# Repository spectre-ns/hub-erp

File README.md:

# hub-erp: an open-source ERP and quality management system where your SOPs are the configuration, and AI agents work under the same rules as people

**hub-erp** is an open-source, self-hosted ERP and quality management system (QMS) built around one idea: the
procedures you already write — SOPs, policies, work instructions — should *be* the system's configuration, not a
description of it. Change a sentence in a policy, put the change through review and approval, and the system's
permissions, routing, approval limits and workflows change with it. AI agents ("cogs") take on routine work beside
your people, as accountable team members: they hold roles, follow the same procedures, act only within criteria the
policy sets, and leave the same signed record a person would.

It is a working prototype, built to explore how far that idea goes in a real business system: purchasing, inventory,
document control, change control, nonconformances and CAPA, complaints, internal audits, management review, design
control, calibration and training.

## What it attempts

- **SOPs as the single source of truth.** Policies are written in plain prose. The hub compiles them into the rules
  it enforces — every rule cites the sentence it came from — and a released policy version is immutable and
  content-addressed. An edit made in Settings or one of the editors becomes a change on a change order, and a cog
  writes it back into the SOP's prose for review, so the configuration never drifts away from the procedures. A
  picture put into an SOP is a question for a person, and a citation of another document is checked, linked, and
  flagged to the SOP's owner when the cited document is retired or superseded.
- **AI agents as governed team members.** Cogs are members of the organization with roles, like anyone else, and no
  outsized permissions. Senior cogs (hosted models) read policy changes and propose the configuration they imply;
  junior cogs (local models) review changes, answer questions and take routine approvals — each within criteria a
  guard checks without any model, so the impact of a wrong judgement stays small. A cog never signs a change to the
  system.
- **Change control for the system itself.** Every configuration change goes through a change order: the cogs compile
  the diff and raise questions, a review panel weighs in, people decide each item (a widening of anyone's authority
  needs two policy owners, and whoever made a change never decides it alone), the change order is signed, and a
  deterministic release — no AI in any step that changes the system — puts exactly what was signed into force.
- **Evidence by default.** Every step of every process lands on an append-only, chained, signed Track; decisions are
  electronic signatures that record who decided, what they saw and what they meant. The design aims at what quality
  standards such as ISO 9001 and ISO 13485 expect of records and signatures.
- **People where judgement matters.** Routine, well-bounded work flows to cogs; anything outside their criteria goes to
  a person, with the reason shown: each item's run page explains, rule by rule, who its approval went to and why.

## Who it is for

- Organizations in quality-driven and regulated industries — manufacturing, engineering, medical devices — that want
  agents to take on routine work without giving up control or traceability.
- Developers and researchers exploring how to govern LLM agents inside business systems: policy-as-prose, guardrails
  that are not models, human approval of configuration, and audit trails that hold up.

hub-erp is a prototype: it has not been validated for production or regulated use, and adopting it for that would
mean validating it as your own quality system requires.

## Make it yours

hub-erp is released under the [MIT license](LICENSE). Every organization's processes are different, so the intent is
that you take this code as a starting point and shape it — the SOPs, the record types, the workflows and the code
itself — around the way your business actually works. The MIT license lets you do that and keep your changes to
yourself: you are free to modify it for your own processes without publishing those modifications. If you build
something you would like to share, contributions are warmly welcome, but never required. (Do keep the license notice
in copies of the code.)

## How it works: six parts

| Part | What it is |
|---|---|
| **Frames** | SOPs, policies and work instructions in prose, compiled into an immutable **policy release** |
| **Cogs** | AI team members with roles: senior cogs compile policy changes, junior cogs review and do routine work |
| **Ops** | Business processes, run as workflows under the release in force; the hub's own automations are Ops too |
| **Guards** | Deterministic checks with no model: grammar and grounding, consistency, widenings, document references, permissions, criteria |
| **Gates** | Where a person, a cog within its criteria, or a committee decides; each decision is an electronic signature |
| **Tracks** | The append-only, chained, signed record of every run |

One record system and one document management system (DMS) span every module. Standard-library Python, SQLite and
files, packaged in a single Docker image. Developer notes: [DEV-NOTES.md](DEV-NOTES.md); for coding agents:
[AGENTS.md](AGENTS.md); the design of change control: [docs/design/change-control.md](docs/design/change-control.md);
the user manual: [docs/manual/](docs/manual/).

## Run it

```bash
docker compose up --build        # http://localhost:8080/ asks who you are; e.g. /?as=alice
```

First start seeds the kernel, installs the ISO 9001 profile, compiles and
releases the first policy release with the two seeded policy owners (bob and
carol), and then makes the SOPs documents: from then on **every configuration
change goes through a change order** (Quality > Change orders); see "Once the
SOPs are documents" below. If that first release fails (for example an org
model with nobody in a routed role) the container prints the Frame to fix,
notes it in `state/.bootstrap-failed`, and still serves the shell with no
release in effect; fix the Frame and run
`docker compose exec hub hubproto bootstrap-release --as bob --second carol`
(run again on a released hub whose SOPs are not documents yet, it converts them).
State lives in the `hub-state` volume and the hub's Frames in the `hub-frames`
volume: the first start fills it with the Frames the image ships, and every
release writes the released texts into it, never into the checkout (the
repository's `frames/` are the example Frames, not a hub's policy). A newer
image's Frames reach a running hub only through a change order. To work on the
checkout's `frames/` and `profiles/` folders from Docker, add
`docker-compose.frames-dir.yml`: a separate development hub (its own Compose
project, containers, image tag and ports; see its header), never the live one. A hub
whose Frames were bind-mounted from the checkout before (issue #5) is moved with
`docs/rollout/frames-volume.md`.

Without Docker (`--root` is the directory holding `frames/` and `state/`;
set `HUBPROTO_ROOT` or pass `--root` when you are not in it):

```bash
python -m venv .venv && . .venv/bin/activate && pip install -e ".[test]"
hubproto init && hubproto seed iso9001 && hubproto bootstrap-release --as bob --second carol
hubproto shell
```

For development, run as many hubs as you like beside the Docker one, each from a
worktree's code, released and with a little demo data, on its own port from 8100
(never 8080, 9980 or 11434), with stand-in models; see DEV-NOTES.md, "Running hubs
for development and for agents" (in a worktree, `python -m hubproto dev ...` runs
that worktree's command line):

```bash
hubproto dev serve --detach --name ws12   # prints http://127.0.0.1:81xx/; open it with ?as=carol
hubproto dev list                         # what runs: name, port, pid, branch, commit, url
hubproto dev stop ws12 && hubproto dev clean ws12
```

Tests: `pip install -r requirements-dev.txt` (pytest and pytest-xdist, development
only), then `python -m pytest -q -n auto` (parallel; without `-n auto` the suite runs
serially and passes that way too).

`hubproto --help` lists every verb in the order an operator uses them, and
`hubproto <verb> --help` explains each flag. Exit codes: 0 done; 1 the hub
refused or the outcome is a failure (error findings, `DENIED`, a failed run);
2 a mistake in the command (unknown id, bad JSON, missing file, wrong root).
A wrong `--root` is refused ("no hub at ..."), never filled with an empty hub.

## After changing Frames (a hub that keeps the Frame files)

A hub bootstrapped with `hubproto bootstrap-release --as bob --second carol
--keep-frame-files "<why>"` (or `sopdocs.keep_frame_files`) skips the
conversion: the Frame files stay the source and the policy owners release
changes without change orders. It is recorded and `status` shows it on every
run; it is meant for work on the Frames themselves and for the test suites
(`tests/conftest.py`'s `release_all` opts out this way), and it ends with
`hubproto sops convert`. On such a hub, edit a sentence in `frames/` on the
host (in Docker: on a development hub from `docker-compose.frames-dir.yml`,
or in the `hub-frames` volume), then compile, have it reviewed and release it. Until the release, the
shell and every run keep applying the release in force (the Frames as they
were released), and on its next start the container says so: `hubproto status
--check` lists the files that differ and prints these commands.

```bash
docker compose exec hub hubproto compile                                  # exit 1 and no release while there are error findings
docker compose exec hub hubproto proposals                                # what is waiting, by number
docker compose exec hub hubproto proposal 3                               # each change with its sentence, file:line and decisions
docker compose exec hub hubproto review 3 --as bob --approve-all --meaning "..."
docker compose exec hub hubproto review 3 --as carol --approve-all        # a widening (a new allow, member, cog route) needs two owners
docker compose exec hub hubproto release 3 --as bob                       # bob or carol: a policy owner of the release in force
docker compose exec hub hubproto releases                                 # versions v1, v2, ... with the digest after
docker compose exec hub hubproto release-diff v2                          # sentences added, removed, changed against v1, and who signed
docker compose run --rm tick                                              # escalate overdue items
```

`compile` refuses to release a heading or a rule-like sentence it could not
read (a `grammar` error with the file and line), a stale proposal (compiled
against an older release than the one in force) is refused with "compile
again", and a release that only re-renders a process is reported as
"re-rendered, no semantic change" instead of a pair of add/remove changes.

Prose that is not in the sentence shapes is read by the compile-frame committee, **as a diff**: an SOP whose text
is the one in force keeps the rules the release read from it, with no model call; a changed SOP's readers get the
unified diff (with line numbers) and the rules in force from it, and answer with rules to add, remove or change and
with **questions** where the changed prose is ambiguous (`proposal["questions"]`; members asking the same thing about
a line make one question; a question the next compile no longer raises is closed). A large diff is read in parts that
fit the model's window. Every change on a proposal says where it came from (`origin`: the SOP, line, words and
reader) and, for a rule a model read, what it means in the hub's own words (`origin.explained`); a reading that drops
or adds a "not" carries a `negation` warning. A rule that only moved in its file (a process below inserted lines) is
listed as moved, not as a change to decide. Direct changes on a change order are put into prose by the qa-manager cog
and compiled back to check they give exactly that rule and nothing else (`hubproto/prose_drafting.py`); the lines it
drafts are credited to it. A reading may touch only the lines that changed: anything else is refused as an `outside-diff`
question (the SOP text is fenced as data in the readers' prompts, so words aimed at the readers are ignored and reported).
A changed sentence that reads like a rule and from which nothing was read, by the grammar or the committee, is a
blocking `unread-rule` question for the committee's chair, also when no model reads here (`convention`).

**The committee reads by consensus.** It is defined on the `senior-cogs` group (organization model, `## Groups`):
the **senior** cogs `senior-organization` and `senior-qa-manager`, bundled with Claude Opus (`claude-opus-5-5`); the
**junior** cogs (`organization`, `qa-manager` and the others, group `junior-cogs`) stay on the local model for
day-to-day work. Each member reads with the model its profile bundles it with,
from its own perspective (its About text, its persona's behaviour and the roles it holds); the diff, the rules in force
and the answer format are the same for every member, so their readings stay comparable.
A rule goes in only when every member reads it the same way; where members read a line differently, the proposal gets
a `disagreement` question quoting the line and each member's reading, for a person to decide. A member whose model is
not available here (not installed, Ollama down, or a `claude-*` model or one of Ollama's cloud models, such as
`gemma4:cloud`, while hosted models are off) is a
`member-unavailable` question naming the committee's chair (`Chair: carol`), who intervenes: the prose of a changed SOP
is not read until it is. **The senior cogs are available only where the administrator has switched hosted models on**
(`HUBPROTO_HOSTED_MODELS=on` with `ANTHROPIC_API_KEY`, under the IT SOP); the call goes through the hub's model gateway
to the Anthropic Messages API. Without them the compiler reads the sentence shapes only and asks about changed prose.
The committee's members change through a change order (the `senior-cogs` group, or a cog's `Model:` line).

**Groups and committees** (change control 11) are also used in processes and on change orders: a process step written
`the design-review committee decides` waits for every member of the committee (people and cogs) and moves only when all
agree; an objection with its reason returns the item; when a cog member's criteria do not hold or a member is late, the
committee's chair intervenes (decide in that member's place, extend the due date, or return the item). A change-control
review sentence may name a committee as reviewers. See DEV-NOTES.md, "Groups and committees".

| Compiler setting | Default | Effect |
|---|---|---|
| `HUBPROTO_EXTRACTOR` | `hybrid` with an Ollama (or with hosted models on and a key), else `convention` | `convention` reads the sentence shapes only (tests, offline use); `hybrid` has the compile-frame committee's cogs read the prose, each with its bundled model. There is no global model override (the old `claude` value is gone and is read as unset) |
| `HUBPROTO_MODEL_MAX_CHARS` | the model's window | the most characters one reading may send; a larger diff is read in parts |

## Once the SOPs are documents: change orders only

The first release converts the SOPs into documents (a hub that kept the Frame
files converts with `hubproto sops convert --as <policy owner>` or Policy >
Convert in the shell). The Frame is then compiled from the SOP documents, and
configuration changes only through a change order (Quality > Change orders);
`status --check` exits 1 on a released hub whose SOPs are not documents and
that did not say it keeps the Frame files. `compile`, `review` and
`release` of a proposal no change order staged, `bootstrap-release --force` and
`seed` are refused (exit 1) with that sentence, and so are the shell's Frame
drafts and proposal actions. The record types in force are kept by the hub from
then on (`state/record-types`): an edited or newly shipped
`config/record-types.json` is reported by `status --check` and not used until a
change order carries what it adds:

```bash
docker compose exec hub hubproto record-types status                       # version in force, history, what the file says differently
docker compose exec hub hubproto record-types carry CO-2026-0004 --from-file --as carol
docker compose exec hub hubproto record-types carry CO-2026-0004 --as carol \
    --changes '[{"op": "add_field", "type": "ncr", "field": "batch", "spec": "text"}]'
```

`docs/design/config-paths.md` lists every path that changes configuration and
what happens on it.

## Who may do what

`hubproto why --as <person> --action create|read|approve --object <bills|documents|...> --folder <Folder>`
answers `ALLOWED` or `DENIED` with the policy sentence and its line (exit 1 on
`DENIED`); the shell's "Why?" link asks the same question. Members, roles and
folders come from the org model in the release in force: `--as`, `--second`,
`--to` and a message's sender must be members (an unknown name is refused
with the member list); only a person may send a message or sign a Gate,
cogs decide only within their `## Approval criteria`. Only a policy owner
may review or release; starting a process needs the first step's role and a
`create` permission; deciding a Gate needs to be an assignee with an
`approve` permission, a meaning for the signature, and the item as it was
seen (`inbox-pending` prints the seen digest and the fields the Gate
accepts). A failed run is the owner's to repair:
`hubproto retry <run> --field k=v --file path`, or `cancel`.

## Cogs are users

A cog is a member of the organization like a person: it holds roles from the org model, is routed work by the
same sentences, is assigned and notified, and signs its decisions through the same path (seen digest, meaning,
signature) with the approval-criteria sentence that let it decide recorded as the delegating rule. The Track of
a bill under the cog's limit reads: assigned to ap-reviewer, reviewed, decided by ap-reviewer (cog); one outside
its criteria reads: assigned to ap-reviewer, reviewed, declined, assigned to dave. Segregation of duties applies
to cogs; a cog supplies no fields at a Gate and may not take an item whose next state needs a person's input.

### Cogs work from queues

Everything asked of a cog lands in its queue, like a task in a person's tray: a comment or chatter message that
mentions it, a message sent to it, an item waiting for it at a Gate, a task given on its profile, a standing duty.
Asking never waits for the cog: the page comes back at once, saying where the request is ("next in its queue",
"3rd in line"), and the chatter shows a "working on it" entry that turns into the answer when it lands, without
a reload (the page polls `/queue-status` and swaps in the parts that changed, so a half-typed message stays put).
A comment saved in the editor is queued the same way, so the save returns at once, and the editor shows which
cog is on it until its reply is written into the comment thread.

Each cog takes one task at a time, oldest first; different cogs work side by side. The queue is a SQLite table
(`state/queue.db`); its modes are set by `HUBPROTO_COG_QUEUE`:

* `worker` (what `hubproto shell` and the compose hub use): a thread in the hub works the queues. It holds the
  hub lock while it reads and writes and gives it up while the model thinks, so pages keep loading during a
  minute-long local answer. `HUBPROTO_COG_WORKERS` (default 1) sets how many tasks run at once across cogs.
* `service`: the hub only queues; `hubproto cog-users --loop 3` (the `cog-users` compose profile) works the
  queues in its own process, the production shape of cogs as service accounts.
* `inline` (library, CLI verbs and tests): a task is worked the moment it is asked, so callers see the result.

A task left "working" by a worker that stopped goes back in the queue when a worker starts (failed after three
tries). A failed task tells the person who asked why. The person who asked, or a policy owner, may withdraw a
task still waiting. Each cog's profile shows its queue (working on, waiting with positions, recently finished);
`/queue` shows every cog's queue on one page, and People shows each cog as free or working.

### The QA manager cog, judgment approvals and assigning work to cogs

`qa-manager` is a cog that works like a QA manager. It holds the quality-manager, reviewer and author roles and
follows the document-control, change-control, NCR and CAPA procedures. It is not on any route, so people stay
first in line. It acts when it is asked:

* **Approving.** "@qa-manager please approve" on an item waiting for people (or `take_turn` in an agent run)
  makes it step in where its approval criteria allow. Its criteria are judgment criteria: `when its review passes`
  makes its model review the item against its procedures and files the review as evidence. In the document-control
  SOP, a minor change is final on its signature. A major change, and any change request, is
  `countersigned by a quality manager`: its signature is recorded and the Gate then waits for a quality manager
  (a person who did not prepare the item). If its review does not pass, the item stays with the people it was
  waiting for. Removing a countersignature from a criterion is a widening, which needs two policy owners.
* **Drafting.** Its `draft_document` tool creates a controlled document with itself as author, written in the
  writing markup, and can send it for approval. Segregation of duties means it never signs its own drafts.
* **Assigned work.** Any item can be assigned to a cog from **Assign** on its page, with an instruction. The cog
  takes it from its queue, works it within its autonomy (looking things up, commenting, reviewing, drafting,
  stepping in to approve) and reports on the chatter. A task filed with a cog as its assignee is the cog's own
  step: it completes it with a summary (`complete_step`) or hands it back to whoever filed it with why
  (`hand_back`). If it does neither, the step goes back to a person automatically.

## Cog profiles, @mentions, committees and swarms

Each cog has a profile in a Frame (`frames/company/cogs.frame.md`): a `## Cog: <name>` section with
`Model:`, `Prompt:` and `Follows:` (the SOPs it follows). The profile is a reviewed rule in the release;
changing it is a widening (two policy owners). A cog is routed work only from processes defined in the SOPs
it follows, as a person is only given work they are trained on; a context cog drafts with its model and prompt
and the text of those SOPs as its only context (`hubproto/model.py`). **A cog is bundled with its model**: `Model: ollama/<name>` is served by that model
in a local Ollama at `HUBPROTO_OLLAMA_URL` (compose reaches the host's Ollama through the `ollama-relay` service),
`Model: claude-*` by Anthropic with `ANTHROPIC_API_KEY`. Nothing stands in: if the model cannot be reached the cog
is not available, so Gates route past it, and chat, mentions, tasks and reviews tell you so. `hubproto models` and
the cog's profile page list the installed models and propose a different one as a policy change; the compiler
warns when a profile names a model this hub cannot use. (Tests and development may set `HUBPROTO_ALLOW_STAND_IN=1`
for a deterministic stand-in.) Models draft and answer; they never sign.

A message about an item (`hubproto msg --record NCR-0001 ...`, or the item's chatter in the shell) acts on its
@mentions: a mentioned **cog** reviews the item against its SOPs, answers in the chatter, files the review as
evidence, and takes its turn at the Gate if the item is waiting for it and the review passed; a mentioned
**person** is asked in their inbox; a mentioned **role** (a committee, people and cogs) fans out to its members;
"please approve" with nothing in flight starts the item's own process, if the sender may. A process step that
names several cogs, `[system] Review the design package (quality-assistant, purchasing-assistant)`, is a swarm:
each reviews from its own SOPs, the findings merge onto the record and into one evidence document, and the
Gate that follows sees them.

## Frames and cog settings as documents

Every Frame (the policy prose the release is compiled from) is also a controlled document in **Policy/Frames**.
"Edit this policy" on it makes a draft, a working Markdown document written in the hub's text editor.
"Check the change" compiles the draft in place of the Frame and shows the rule changes, the findings and a diff;
"Propose for release" makes it a proposal, which the policy owners review and release on the proposal page.
Releasing writes the draft into the Frame file (raising its version) and makes it the effective version of the
Frame's document. A recompile from the CLI carries an open draft forward instead of dropping it.

Cog settings are Frames too: a cog's model, prompt and the SOPs it follows are its `## Cog:` section in
`cogs.frame.md`; its roles and the permissions that come with them are in the organization model. A profile may
also link documents: `Prompt from: DOC-0123` takes the prompt from a document, `References: DOC-0200, DOC-0201`
adds documents the cog works from. Each release pins the version it compiled, so a cog reads exactly what was
reviewed; a newer version of a linked document is a change the policy owners approve when they next release.
The cog's profile page shows the pinned documents and links to its profile and the organization model.

The messenger in the bottom-right corner of every page is an informal chat with a cog: it knows the page you
are on, the procedures it follows and its queue, remembers the conversation, and changes nothing; reviews,
edits and approvals go through the item's chatter, comments or Ops.

## The agent harness: cogs working on their own

A cog can be handed a task ("find nonconformances older than a week and remind their owners") from its profile
page or `hubproto agent --cog quality-assistant --as carol --goal "..."`, and takes up the `Duty:` lines in its
profile once a day (`hubproto agent-duties`, or the `agents` compose profile). Its model plans and calls tools:
the record tools to look (search, read records and documents, queues, history, counts) and action tools to act.
It acts **as itself** and only through governed paths: commenting on an item, messaging a person, starting a
process (the runner checks it may), taking its own turn at a Gate (bound by its approval criteria), reviewing a
document (filed as evidence) and editing a working document. It never writes record fields directly; when the
system refuses, the run says so.

- **Autonomy** is a line in the cog's profile: `read` (look and report), `propose` (actions wait for the person
  who gave the task, or a policy owner, to confirm them on the run page) or `act`. Changing it is a widening.
- **Budget**: at most 5 actions and 10 steps a run (`HUBPROTO_AGENT_ACTIONS`, `HUBPROTO_AGENT_ROUNDS`).
- **Audit**: every step of a run is on its Track (`state/agents/<run>.jsonl`, the run page); the person who gave
  the task is told what was done.
- **Kill switch**: `HUBPROTO_AGENTS=off`.

The same record tools are served over MCP at `POST /mcp?as=<member>` (JSON-RPC: initialize, tools/list,
tools/call), trimmed to what that member may read, so any MCP client can look at the record space.

**New cogs and people** are added from the People page (or `hub.propose_new_cog` / `propose_new_person`): the
form drafts the change to the organization model (and, for a cog, its profile) as one policy proposal for the
policy owners. A cog needs no code: a profile is enough; on release the hub installs it as a working cog.

## The integrated editor

Documents open in Collabora Online inside the hub: the hub is a WOPI host (`hubproto/wopi.py`; the
endpoints are under `/wopi/files/<number>`), so SharePoint's Office Online or any other WOPI client
could stand in for Collabora in production. `docker compose up` starts Collabora beside the hub.

- "New document" on a folder page or an item creates a blank .docx, .xlsx, .odt, .ods, .md or .txt
  (a *working* document) and opens it. "Edit online" on a document page opens an existing one.
- Opening the editor checks the document out to you; every save is a minor version noted "saved in
  the editor"; "Finish editing" releases it. Someone else's check-out, an *effective* controlled
  document, and evidence or external files open read-only (a controlled document changes only
  through a new revision via document-control).
- Settings: `HUBPROTO_COLLABORA_URL` (the editor as the browser reaches it), `HUBPROTO_WOPI_BASE`
  (this hub as the editor reaches it), `HUBPROTO_COLLABORA_DISCOVERY` (where the hub reads the
  editor's discovery document), `HUBPROTO_PUBLIC_URL` (this hub's origin, for the editor's frame
  policy). Without them the editor page says how to configure it and documents stay downloadable
  and check-in-able. Set `HUBPROTO_SECRET` to keep editor sessions valid across hub restarts.

## Targeted edits to documents

When a comment or a chatter message asks a cog to change a document ("delete the Records section", "say must,
not shall"), the cog answers with a short list of operations rather than a whole new text
(`hubproto/edits.py`; the cog's edit task is in `hubproto/cogs.py`). An operation is a line starting `@@`; the
lines after it, up to the next `@@`, are its content in the writing markup (headings, bullets, `| a | b |` tables).

Text documents (docx, odt, md, txt):

    @@ insert at start          @@ insert at end
    @@ insert after: <text>     @@ insert before: <text>     @@ append to section: <heading>
    @@ replace: <exact text>    @@ with: <new text>          (every occurrence, inside its paragraph)
    @@ replace paragraph: <text>    @@ replace section: <heading>    @@ rewrite
    @@ delete: <exact text>     @@ delete paragraph: <text>  @@ delete section: <heading>

Spreadsheets (xlsx, ods):

    @@ append rows   @@ insert rows at: <n>   @@ set: B3: <value>   @@ clear: B2:D4
    @@ delete rows: 4-6   @@ replace: <text>  @@ with: <text>

- Applied in the file, the operations keep the document's formatting. A replacement touches only the part that
  differs ("suppliers shall be" to "suppliers must be" rewrites "shall" alone), so the runs around it keep their
  bold or italic. Comment anchors in removed paragraphs move to the nearest paragraph that stays, so no comment
  is lost. Text is matched exactly first, then ignoring case, curly quotes and non-breaking spaces. Deleting the
  whole text of a paragraph removes the paragraph.
- Each operation is reported: the cog's reply on the chatter lists the changes, and anything that could not be
  done (text not found, no section with that heading) is said in a follow-up from the cog.
- **Live or in the file.** When someone has the document open in the editor, the cog's seat (its own editor
  session) does live only what is safe from outside the editor: find-and-replace and deleting text, and inserting
  headings and paragraphs at the very start or end of the document; in a spreadsheet, setting cells and appending
  rows. Everything else (inserting after or before a paragraph, deleting or replacing paragraphs and sections,
  tables, lists, row moves, rewrites) is done by the hub in the file once the session has saved, and the editor
  reloads. Placing the cursor at a paragraph found by search is not reliable from outside the editor: in a live
  test, text typed after the search replaced the found paragraph instead of following it.
- **The check after a live edit.** Once the seat is done and the session has saved, the editor page posts to
  `/verify-edit`. The hub checks each operation in the saved file, including that an insert landed right after
  or before its target. An insert that landed in the wrong place is taken out and done again in the right place;
  any operation that did not take is finished in the file (a new version by the hub, and the editor reloads). The
  report is kept on the cog's reply (`edit_report`), and failures are said on the chatter.
- With nobody in the editor, the hub applies the operations in the file at once (`WopiHost.apply_replies`).
  The agent harness's `edit_document` tool uses the same operations.
- Limits: formulas are not adjusted when rows move; merged cells and charts are not edited; spreadsheet
  operations apply to the first sheet only.

## Backup and restore

The state is one SQLite file plus directories under `state/`: `kernel.db`,
`runs/` (one directory per run with its Track), `releases/` (bundles and
`index.json`), `proposals/`, `blobs/` and `inbox/`. They reference each other
(a record names its run and release, a run is pinned to a release digest), so
a backup is only usable as a whole. The backup also holds the hub's Frames
(`frames/`, in Docker the `hub-frames` volume), which the releases write. They
are copied after the kernel's snapshot, with no lock: a release during a backup
of a running hub can leave Frames newer than the state, which a restore then
reports as drift (it prints what `status --check` will say). Stop the hub for a
backup consistent across all parts.

```bash
docker compose exec hub hubproto backup /hub/state/backups/2026-11-06   # a new or empty directory
docker compose cp hub:/hub/state/backups/2026-11-06 ./backup-2026-11-06
```

`backup` copies `kernel.db` through the SQLite backup API (a consistent
snapshot even while the shell is running) and the directories as files. For
a copy that is consistent across all of them, stop the shell first
(`docker compose stop hub`) or run the backup when nobody is working.

```bash
docker compose stop hub
docker compose run --rm --entrypoint hubproto hub restore /hub/state/backups/2026-11-06 --force
docker compose start hub
```

`restore` refuses a partial set (every part must be present) and refuses to
overwrite a live state without `--force`; with it the previous state is moved
beside the new one (`state.before-restore-<time>`), or, when `state/` cannot be
renamed (in the container it is the volume's mount point) or holds the backup
being restored (`/hub/state/backups/...` above), into
`state/.before-restore-<time>/`, leaving the backups folder where it is; the
command above works in the container as written. The Frames in the backup
replace the hub's (the ones replaced are kept in `frames/.before-restore-<time>/`);
a backup made before backups held the Frames, or one with no Frame files in its
`frames/`, restores the state and leaves the Frames as they are. `restore` then
says whether the Frames match the restored release, listing any that differ. `hubproto status` then shows the release in force and the
run counts.

## What it demonstrates

| Claim in the plan | Where it is proven |
|---|---|
| Permissions, routing, processes and workflows come from prose | `frames/**` and `profiles/iso9001/frames/**` are the only policy input; `hubproto compile` turns sentences into rules with citations |
| A release is deterministic and content-addressed | `release.py`: SHA-256 of the rendered bundle without citations; a no-op edit yields the same digest |
| Changes are gated by people; widenings need two | `compile.py`: per-change decisions; widenings need two policy owners |
| Every record type has a workflow derived from its SOP | `release.render_workflow`: states, human and automatic transitions, SLAs, rejection returns from the process section |
| Items follow the release in force from their next move | `runner.py`: a run keeps its state when a new release comes into force and follows that release from its next move; state maps move items out of statuses a release removes |
| One record system for all modules | `kernel.py`: types, numbering, states, typed links, labels, holds, history; `config/record-types.json` |
| A DMS with classes, versions, check-out and attachments | `dms.py`: blob store, versions, controlled/evidence/external/working/template classes, snapshots with signature pages, email and upload intake |
| Cogs are team members | The org model lists `ap-reviewer`, `doc-reviewer` and `quality-assistant` as members with roles; they receive routed approvals, DMs and email, file records, and approve only within `## Approval criteria` |
| Segregation of duties binds cogs too | A cog that filed an item is skipped as its approver and a person decides |
| Only code Cogs write, only under a grant | `ledger-poster`, `document-publisher`, `capa-opener`, `ncr-opener` refuse without a grant; child processes inherit admission from the parent's grant |
| SLAs and escalation in prose | "Disposition the nonconformance in nonconformance is due within 5 days." "Overdue items in nonconformance go to the management representative." `hubproto tick` escalates |
| Every decision is evidence | Track entries carry release digest, manifest digest, Cog versions, Guard problems, Gate verdicts, the delegating sentence for a cog decision, and a signature digest |
| An ISO 9001 seed profile | `profiles/iso9001/`: quality manual, SOPs, work instructions, templates, clause map; `hubproto conformance` prints the coverage |
| Policy owners can see what a release changed | `hubproto release-diff v<n>`: sentences added, removed and changed against the parent by Frame and file line, with each owner's decisions; `hubproto proposal <n>`: every change with its sentence and decisions |

## Layout

```
frames/              the example company's Frames (org-model is the scope root); a new hub starts from them
profiles/iso9001/    the seed profile: frames, templates, clause map
config/              record types, link vocabulary, retention classes (versioned configuration)
hubproto/            see DEV-NOTES.md for the module map and APIs
tests/               pytest suites
docker/, Dockerfile, docker-compose.yml, docker-compose.frames-dir.yml (development: Frames from the checkout)
```

## Deviations from the published specs, on purpose

* Op manifests are JSON generated from `## Process:` sections under a local
  profile (`hubproto/op-manifest [0.1]`), not `openteams/op-manifest [0.2]`.
* Gates decided by a cog under approval criteria are an extension of the
  published profile; the Track records the delegating sentence with every
  cog decision.
* Everything runs in one process with files and SQLite. The production shape
  (Collab Hub run API, Harbor digests, OpenFGA, Postgres, Keycloak, Collabora,
  Tika, Gotenberg) keeps the same seams.

## License

MIT — see [LICENSE](LICENSE). Copyright (c) 2026 The hub-erp authors. You may use, modify and distribute hub-erp,
including in private, modified form for your own business processes; keep the license notice in copies of the code.

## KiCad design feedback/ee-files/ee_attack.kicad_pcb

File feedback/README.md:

# Acceptance-testing panel

Each panelist exercises the hub as one kind of user, writes findings to
`feedback/<persona>.md`, and the maintainer triages them in
`feedback/TRIAGE.md`. Findings are the only output that counts; praise is
noise.

## Where the hub is

- Shell: `http://localhost:8080/?as=<principal>` (identity is the `as`
  parameter; no SSO in the prototype). Members and their roles are on
  `/admin`. People: alice (finance clerk, author, design engineer), bob
  (controller, reviewer, policy owner, management representative, internal
  auditor, design authority), carol (quality manager, reviewer, policy owner,
  document controller), dave (payables reviewer). Cogs: ap-reviewer,
  doc-reviewer, quality-assistant.
- CLI inside the container: `docker compose exec hub hubproto <command>`
  (`hubproto --help`), or locally `. .venv/bin/activate && hubproto --root . <command>`
  against a local state directory.
- Frames (the policy prose) are under `frames/` and `profiles/iso9001/frames/`;
  the grammar is in `frames/reference/writing-policy-frames.frame.md` and
  `DEV-NOTES.md`.
- The plan the product is built from is the "Intelligence Hub ERP Plan"
  artifact; `README.md` summarizes the claims.

## Finding format

```
### F-<persona>-<n>: <one-line title>
Severity: blocker | major | minor | question
Area: shell | CLI | workflow | records | DMS | policy | docs | security | performance | architecture
Steps: numbered, exact (URLs, principals, inputs)
Expected:
Actual:
Evidence: paths, output, record numbers, run ids
Suggested fix (optional):
```

Rules for panelists: act in character for your role and only use what a
person in that role would use; do not fix anything; do not edit files outside
`feedback/`; prefer real reproduction over speculation; when a feature is
missing rather than broken, say "missing" and what you expected instead.

## The scenario every panelist must drive end to end

Design documentation to an order from an approved vendor, then receipt and
payment. Use the shell (`/` Start forms, `/inbox`, `/record/...`, `/boards`)
and, where your role would, the CLI.

1. As alice (design engineer): start `design-release` with a title, kind
   `electrical`, two user needs (free text), and the two example files
   `examples/sensor.kicad_sch` and `examples/box.FCStd` attached. Expect:
   two requirement records waiting for bob, a requirements trace, a BOM,
   an ERC report and a STEP export on the design record, and the design
   waiting for bob with risk `high` (requirements not yet accepted).
2. As bob (design authority): accept both requirements from the inbox,
   supplying acceptance criteria and a verification method. Then review the
   design. Expect: after approval the part is released, an inventory item is
   created for the unknown BOM line, and purchase requests appear for the
   shortages.
3. Purchasing: the small request for the known item from the approved
   supplier is approved by the purchasing-assistant cog and a PO is issued;
   the request with no supplier waits for dave (buyer), who approves it
   naming `acme-metals` and a unit cost. A request over 10,000 USD must go to
   bob (controller). A request naming `newco-tools` (not approved) must never
   be approved by the cog.
4. As alice or dave: start `goods-receipt` for the PO; dave confirms; the
   item's stock rises and the PO is marked received.
5. As alice: start `purchase-to-pay` with a bill against that PO number.
   Expect a matched bill, cog approval within criteria, and a balanced
   journal in `/files?folder=Finance`.
6. Check the Track of every run, the Why links, the snapshot documents, and
   the boards for `design`, `requirement`, `purchase-request`, `item`.

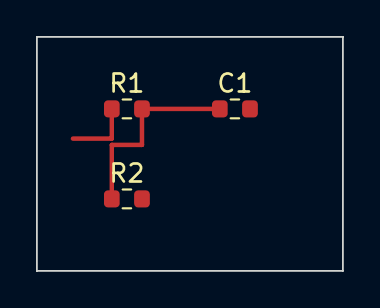
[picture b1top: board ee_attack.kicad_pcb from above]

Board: 2 copper layers, 17.0 x 13.0 mm, 3 parts (0 on the bottom side), 2 nets.

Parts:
C1: 100n; R_0603_1608Metric
R1, R2: 10k; R_0603_1608Metric

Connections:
GND: C1.2, R2.2
VDIV: C1.1, R1.2, R2.1
